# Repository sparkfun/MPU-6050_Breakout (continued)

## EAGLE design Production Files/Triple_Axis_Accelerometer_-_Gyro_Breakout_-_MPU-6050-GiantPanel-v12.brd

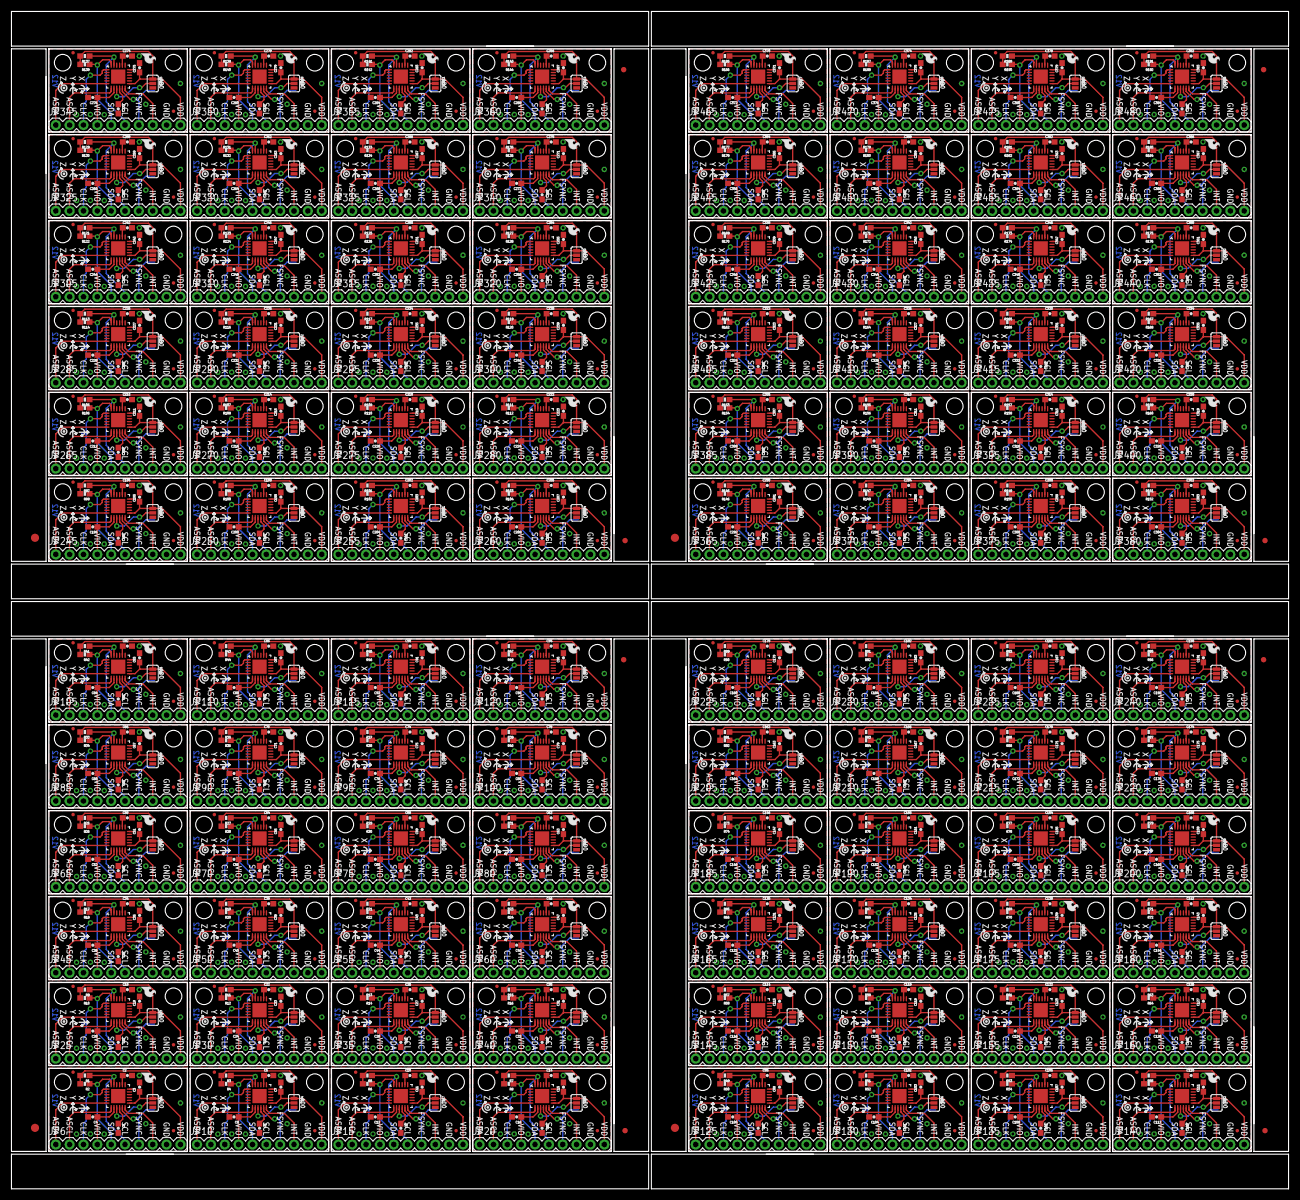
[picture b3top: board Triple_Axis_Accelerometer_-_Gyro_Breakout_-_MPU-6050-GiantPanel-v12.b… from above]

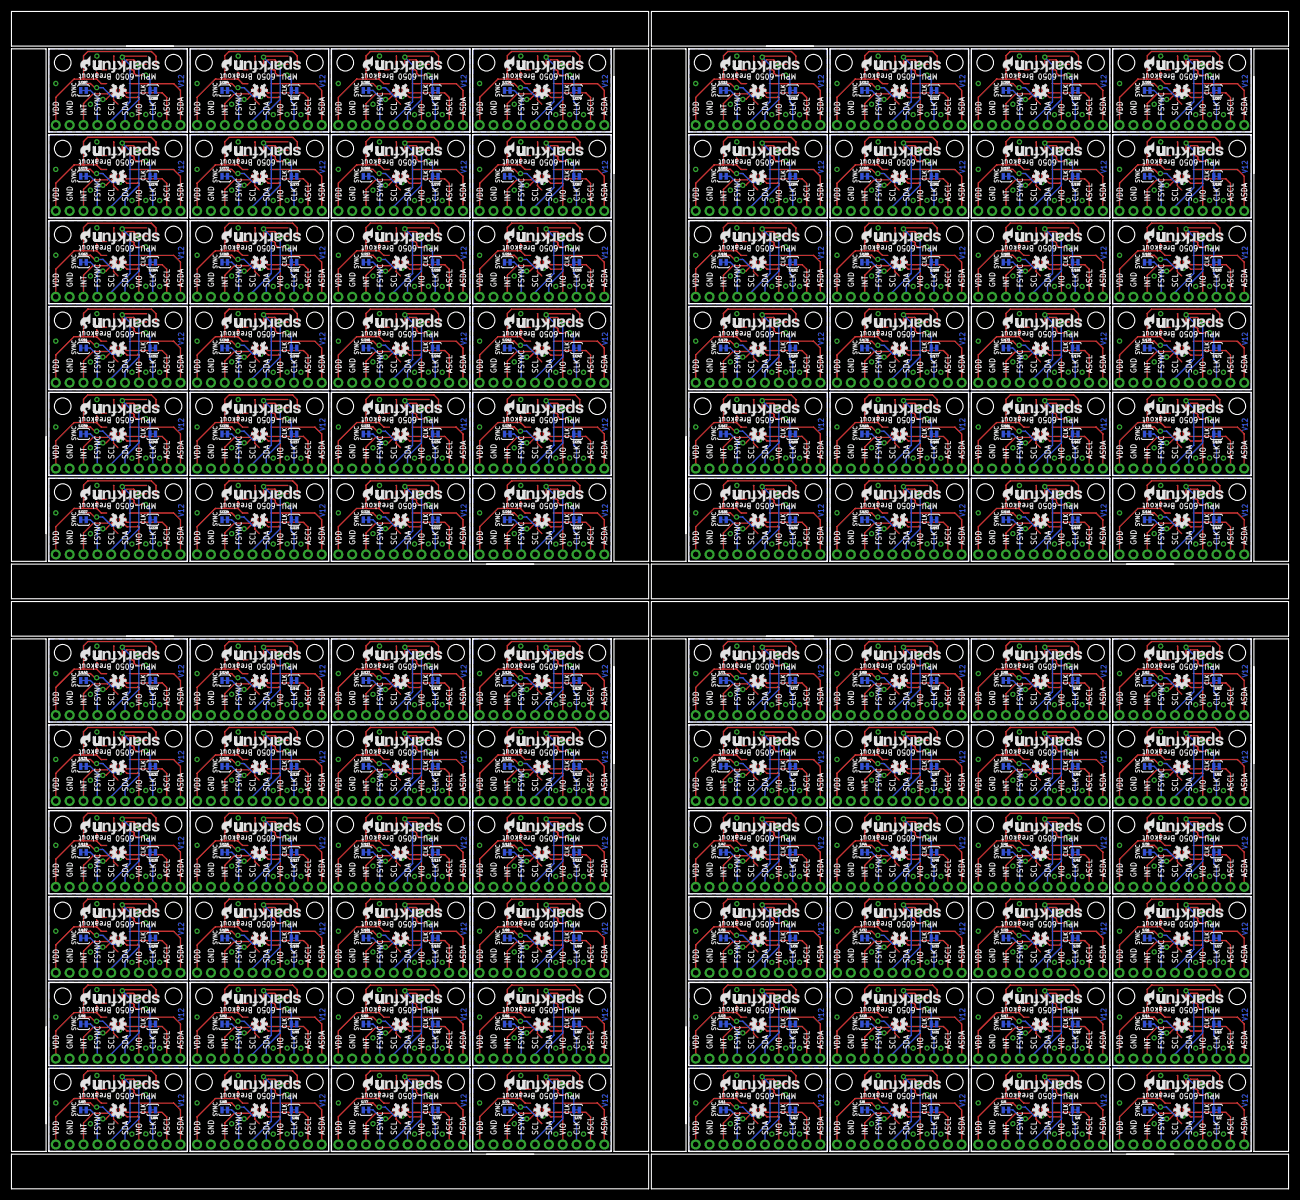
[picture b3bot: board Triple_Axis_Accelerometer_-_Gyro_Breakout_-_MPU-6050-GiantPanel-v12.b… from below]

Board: 2 copper layers, 234.2 x 215.9 mm, 1836 parts (480 on the bottom side), 1248 nets.

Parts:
C1, C3, C5, C7, C9, C11, C13, C15, C17, C19, C21, C23, C25, C27, C29, C31, C33, C35, C37, C39, C41, C43, C45, C47, C49, C51, C53, C55, C57, C59, C61, C63, C65, C67, C69, C71, C73, C75, C77, C79, C81, C83, C85, C87, C89, C91, C93, C95, C97, C99, C101, C103, C105, C107, C109, C111, C113, C115, C117, C119, C121, C123, C125, C127, C129, C131, C133, C135, C137, C139, C141, C143, C145, C147, C149, C151, C153, C155, C157, C159, C161, C163, C165, C167, C169, C171, C173, C175, C177, C179, C181, C183, C185, C187, C189, C191, C193, C195, C197, C199, C201, C203, C205, C207, C209, C211, C213, C215, C217, C219, C221, C223, C225, C227, C229, C231, C233, C235, C237, C239, C241, C243, C245, C247, C249, C251, C253, C255, C257, C259, C261, C263, C265, C267, C269, C271, C273, C275, C277, C279, C281, C283, C285, C287, C289, C291, C293, C295, C297, C299, C301, C303, C305, C307, C309, C311, C313, C315, C317, C319, C321, C323, C325, C327, C329, C331, C333, C335, C337, C339, C341, C343, C345, C347, C349, C351, C353, C355, C357, C359, C361, C363, C365, C367, C369, C371, C373, C375, C377, C379, C381, C383: 0.1uF; 0603-CAP
C2, C6, C10, C14, C18, C22, C26, C30, C34, C38, C42, C46, C50, C54, C58, C62, C66, C70, C74, C78, C82, C86, C90, C94, C98, C102, C106, C110, C114, C118, C122, C126, C130, C134, C138, C142, C146, C150, C154, C158, C162, C166, C170, C174, C178, C182, C186, C190, C194, C198, C202, C206, C210, C214, C218, C222, C226, C230, C234, C238, C242, C246, C250, C254, C258, C262, C266, C270, C274, C278, C282, C286, C290, C294, C298, C302, C306, C310, C314, C318, C322, C326, C330, C334, C338, C342, C346, C350, C354, C358, C362, C366, C370, C374, C378, C382: 2.2nF; 0603-CAP
C4, C8, C12, C16, C20, C24, C28, C32, C36, C40, C44, C48, C52, C56, C60, C64, C68, C72, C76, C80, C84, C88, C92, C96, C100, C104, C108, C112, C116, C120, C124, C128, C132, C136, C140, C144, C148, C152, C156, C160, C164, C168, C172, C176, C180, C184, C188, C192, C196, C200, C204, C208, C212, C216, C220, C224, C228, C232, C236, C240, C244, C248, C252, C256, C260, C264, C268, C272, C276, C280, C284, C288, C292, C296, C300, C304, C308, C312, C316, C320, C324, C328, C332, C336, C340, C344, C348, C352, C356, C360, C364, C368, C372, C376, C380, C384: 10nF; 0603-CAP
E$1, E$6, E$9, E$12: FIDUCIAL-1.5X3
E$2, E$3, E$4, E$5, E$7, E$8, E$10, E$11: FIDUCIAL-1X2
JP1, JP3, JP4, JP7, JP11, JP12, JP16, JP17, JP21, JP22, JP26, JP27, JP31, JP32, JP36, JP37, JP41, JP42, JP46, JP47, JP51, JP52, JP56, JP57, JP61, JP62, JP66, JP67, JP71, JP72, JP76, JP77, JP81, JP82, JP86, JP87, JP91, JP92, JP96, JP97, JP101, JP102, JP106, JP107, JP111, JP112, JP116, JP117, JP121, JP122, JP126, JP127, JP131, JP132, JP136, JP137, JP141, JP142, JP146, JP147, JP151, JP152, JP156, JP157, JP161, JP162, JP166, JP167, JP171, JP172, JP176, JP177, JP181, JP182, JP186, JP187, JP191, JP192, JP196, JP197, JP201, JP202, JP206, JP207, JP211, JP212, JP216, JP217, JP221, JP222, JP226, JP227, JP231, JP232, JP236, JP237, JP241, JP242, JP246, JP247, JP251, JP252, JP256, JP257, JP261, JP262, JP266, JP267, JP271, JP272, JP276, JP277, JP281, JP282, JP286, JP287, JP291, JP292, JP296, JP297, JP301, JP302, JP306, JP307, JP311, JP312, JP316, JP317, JP321, JP322, JP326, JP327, JP331, JP332, JP336, JP337, JP341, JP342, JP346, JP347, JP351, JP352, JP356, JP357, JP361, JP362, JP366, JP367, JP371, JP372, JP376, JP377, JP381, JP382, JP386, JP387, JP391, JP392, JP396, JP397, JP401, JP402, JP406, JP407, JP411, JP412, JP416, JP417, JP421, JP422, JP426, JP427, JP431, JP432, JP436, JP437, JP441, JP442, JP446, JP447, JP451, JP452, JP456, JP457, JP461, JP462, JP466, JP467, JP471, JP472, JP476, JP477: STAND-OFFTIGHT; STAND-OFF-TIGHT
JP2, JP5, JP8, JP9, JP13, JP14, JP18, JP19, JP23, JP24, JP28, JP29, JP33, JP34, JP38, JP39, JP43, JP44, JP48, JP49, JP53, JP54, JP58, JP59, JP63, JP64, JP68, JP69, JP73, JP74, JP78, JP79, JP83, JP84, JP88, JP89, JP93, JP94, JP98, JP99, JP103, JP104, JP108, JP109, JP113, JP114, JP118, JP119, JP123, JP124, JP128, JP129, JP133, JP134, JP138, JP139, JP143, JP144, JP148, JP149, JP153, JP154, JP158, JP159, JP163, JP164, JP168, JP169, JP173, JP174, JP178, JP179, JP183, JP184, JP188, JP189, JP193, JP194, JP198, JP199, JP203, JP204, JP208, JP209, JP213, JP214, JP218, JP219, JP223, JP224, JP228, JP229, JP233, JP234, JP238, JP239, JP243, JP244, JP248, JP249, JP253, JP254, JP258, JP259, JP263, JP264, JP268, JP269, JP273, JP274, JP278, JP279, JP283, JP284, JP288, JP289, JP293, JP294, JP298, JP299, JP303, JP304, JP308, JP309, JP313, JP314, JP318, JP319, JP323, JP324, JP328, JP329, JP333, JP334, JP338, JP339, JP343, JP344, JP348, JP349, JP353, JP354, JP358, JP359, JP363, JP364, JP368, JP369, JP373, JP374, JP378, JP379, JP383, JP384, JP388, JP389, JP393, JP394, JP398, JP399, JP403, JP404, JP408, JP409, JP413, JP414, JP418, JP419, JP423, JP424, JP428, JP429, JP433, JP434, JP438, JP439, JP443, JP444, JP448, JP449, JP453, JP454, JP458, JP459, JP463, JP464, JP468, JP469, JP473, JP474, JP478, JP479: FIDUCIALUFIDUCIAL; MICRO-FIDUCIAL
JP6, JP10, JP15, JP20, JP25, JP30, JP35, JP40, JP45, JP50, JP55, JP60, JP65, JP70, JP75, JP80, JP85, JP90, JP95, JP100, JP105, JP110, JP115, JP120, JP125, JP130, JP135, JP140, JP145, JP150, JP155, JP160, JP165, JP170, JP175, JP180, JP185, JP190, JP195, JP200, JP205, JP210, JP215, JP220, JP225, JP230, JP235, JP240, JP245, JP250, JP255, JP260, JP265, JP270, JP275, JP280, JP285, JP290, JP295, JP300, JP305, JP310, JP315, JP320, JP325, JP330, JP335, JP340, JP345, JP350, JP355, JP360, JP365, JP370, JP375, JP380, JP385, JP390, JP395, JP400, JP405, JP410, JP415, JP420, JP425, JP430, JP435, JP440, JP445, JP450, JP455, JP460, JP465, JP470, JP475, JP480: M10"; 1X10
R1, R2, R3, R4, R5, R6, R7, R8, R9, R10, R11, R12, R13, R14, R15, R16, R17, R18, R19, R20, R21, R22, R23, R24, R25, R26, R27, R28, R29, R30, R31, R32, R33, R34, R35, R36, R37, R38, R39, R40, R41, R42, R43, R44, R45, R46, R47, R48, R49, R50, R51, R52, R53, R54, R55, R56, R57, R58, R59, R60, R61, R62, R63, R64, R65, R66, R67, R68, R69, R70, R71, R72, R73, R74, R75, R76, R77, R78, R79, R80, R81, R82, R83, R84, R85, R86, R87, R88, R89, R90, R91, R92, R93, R94, R95, R96, R97, R98, R99, R100, R101, R102, R103, R104, R105, R106, R107, R108, R109, R110, R111, R112, R113, R114, R115, R116, R117, R118, R119, R120, R121, R122, R123, R124, R125, R126, R127, R128, R129, R130, R131, R132, R133, R134, R135, R136, R137, R138, R139, R140, R141, R142, R143, R144, R145, R146, R147, R148, R149, R150, R151, R152, R153, R154, R155, R156, R157, R158, R159, R160, R161, R162, R163, R164, R165, R166, R167, R168, R169, R170, R171, R172, R173, R174, R175, R176, R177, R178, R179, R180, R181, R182, R183, R184, R185, R186, R187, R188, R189, R190, R191, R192: 10k; 0603-RES
SJ1, SJ4, SJ7, SJ10, SJ13, SJ16, SJ19, SJ22, SJ25, SJ28, SJ31, SJ34, SJ37, SJ40, SJ43, SJ46, SJ49, SJ52, SJ55, SJ58, SJ61, SJ64, SJ67, SJ70, SJ73, SJ76, SJ79, SJ82, SJ85, SJ88, SJ91, SJ94, SJ97, SJ100, SJ103, SJ106, SJ109, SJ112, SJ115, SJ118, SJ121, SJ124, SJ127, SJ130, SJ133, SJ136, SJ139, SJ142, SJ145, SJ148, SJ151, SJ154, SJ157, SJ160, SJ163, SJ166, SJ169, SJ172, SJ175, SJ178, SJ181, SJ184, SJ187, SJ190, SJ193, SJ196, SJ199, SJ202, SJ205, SJ208, SJ211, SJ214, SJ217, SJ220, SJ223, SJ226, SJ229, SJ232, SJ235, SJ238, SJ241, SJ244, SJ247, SJ250, SJ253, SJ256, SJ259, SJ262, SJ265, SJ268, SJ271, SJ274, SJ277, SJ280, SJ283, SJ286: SJ_3_PASTE2&3
SJ2, SJ3, SJ5, SJ6, SJ8, SJ9, SJ11, SJ12, SJ14, SJ15, SJ17, SJ18, SJ20, SJ21, SJ23, SJ24, SJ26, SJ27, SJ29, SJ30, SJ32, SJ33, SJ35, SJ36, SJ38, SJ39, SJ41, SJ42, SJ44, SJ45, SJ47, SJ48, SJ50, SJ51, SJ53, SJ54, SJ56, SJ57, SJ59, SJ60, SJ62, SJ63, SJ65, SJ66, SJ68, SJ69, SJ71, SJ72, SJ74, SJ75, SJ77, SJ78, SJ80, SJ81, SJ83, SJ84, SJ86, SJ87, SJ89, SJ90, SJ92, SJ93, SJ95, SJ96, SJ98, SJ99, SJ101, SJ102, SJ104, SJ105, SJ107, SJ108, SJ110, SJ111, SJ113, SJ114, SJ116, SJ117, SJ119, SJ120, SJ122, SJ123, SJ125, SJ126, SJ128, SJ129, SJ131, SJ132, SJ134, SJ135, SJ137, SJ138, SJ140, SJ141, SJ143, SJ144, SJ146, SJ147, SJ149, SJ150, SJ152, SJ153, SJ155, SJ156, SJ158, SJ159, SJ161, SJ162, SJ164, SJ165, SJ167, SJ168, SJ170, SJ171, SJ173, SJ174, SJ176, SJ177, SJ179, SJ180, SJ182, SJ183, SJ185, SJ186, SJ188, SJ189, SJ191, SJ192, SJ194, SJ195, SJ197, SJ198, SJ200, SJ201, SJ203, SJ204, SJ206, SJ207, SJ209, SJ210, SJ212, SJ213, SJ215, SJ216, SJ218, SJ219, SJ221, SJ222, SJ224, SJ225, SJ227, SJ228, SJ230, SJ231, SJ233, SJ234, SJ236, SJ237, SJ239, SJ240, SJ242, SJ243, SJ245, SJ246, SJ248, SJ249, SJ251, SJ252, SJ254, SJ255, SJ257, SJ258, SJ260, SJ261, SJ263, SJ264, SJ266, SJ267, SJ269, SJ270, SJ272, SJ273, SJ275, SJ276, SJ278, SJ279, SJ281, SJ282, SJ284, SJ285, SJ287, SJ288: SJ_2S-TRACE
U1, U2, U3, U4, U5, U6, U7, U8, U9, U10, U11, U12, U13, U14, U15, U16, U17, U18, U19, U20, U21, U22, U23, U24, U25, U26, U27, U28, U29, U30, U31, U32, U33, U34, U35, U36, U37, U38, U39, U40, U41, U42, U43, U44, U45, U46, U47, U48, U49, U50, U51, U52, U53, U54, U55, U56, U57, U58, U59, U60, U61, U62, U63, U64, U65, U66, U67, U68, U69, U70, U71, U72, U73, U74, U75, U76, U77, U78, U79, U80, U81, U82, U83, U84, U85, U86, U87, U88, U89, U90, U91, U92, U93, U94, U95, U96: MPU-6050-1; QFN-24-4MM2
U$1, U$6, U$10, U$14, U$18, U$22, U$26, U$30, U$34, U$38, U$42, U$46, U$50, U$54, U$58, U$62, U$66, U$70, U$74, U$78, U$82, U$86, U$90, U$94, U$98, U$102, U$106, U$110, U$114, U$118, U$122, U$126, U$130, U$134, U$138, U$142, U$146, U$150, U$154, U$158, U$162, U$166, U$170, U$174, U$178, U$182, U$186, U$190, U$194, U$198, U$202, U$206, U$210, U$214, U$218, U$222, U$226, U$230, U$234, U$238, U$242, U$246, U$250, U$254, U$258, U$262, U$266, U$270, U$274, U$278, U$282, U$286, U$290, U$294, U$298, U$302, U$306, U$310, U$314, U$318, U$322, U$326, U$330, U$334, U$338, U$342, U$346, U$350, U$354, U$358, U$362, U$366, U$370, U$374, U$378, U$382: OSHW-LOGOS; OSHW-LOGO-S
U$2, U$3, U$5, U$7, U$9, U$11, U$13, U$15, U$17, U$19, U$21, U$23, U$25, U$27, U$29, U$31, U$33, U$35, U$37, U$39, U$41, U$43, U$45, U$47, U$49, U$51, U$53, U$55, U$57, U$59, U$61, U$63, U$65, U$67, U$69, U$71, U$73, U$75, U$77, U$79, U$81, U$83, U$85, U$87, U$89, U$91, U$93, U$95, U$97, U$99, U$101, U$103, U$105, U$107, U$109, U$111, U$113, U$115, U$117, U$119, U$121, U$123, U$125, U$127, U$129, U$131, U$133, U$135, U$137, U$139, U$141, U$143, U$145, U$147, U$149, U$151, U$153, U$155, U$157, U$159, U$161, U$163, U$165, U$167, U$169, U$171, U$173, U$175, U$177, U$179, U$181, U$183, U$185, U$187, U$189, U$191, U$193, U$195, U$197, U$199, U$201, U$203, U$205, U$207, U$209, U$211, U$213, U$215, U$217, U$219, U$221, U$223, U$225, U$227, U$229, U$231, U$233, U$235, U$237, U$239, U$241, U$243, U$245, U$247, U$249, U$251, U$253, U$255, U$257, U$259, U$261, U$263, U$265, U$267, U$269, U$271, U$273, U$275, U$277, U$279, U$281, U$283, U$285, U$287, U$289, U$291, U$293, U$295, U$297, U$299, U$301, U$303, U$305, U$307, U$309, U$311, U$313, U$315, U$317, U$319, U$321, U$323, U$325, U$327, U$329, U$331, U$333, U$335, U$337, U$339, U$341, U$343, U$345, U$347, U$349, U$351, U$353, U$355, U$357, U$359, U$361, U$363, U$365, U$367, U$369, U$371, U$373, U$375, U$377, U$379, U$381, U$383: SFE-LOGO-FLAME
U$4, U$8, U$12, U$16, U$20, U$24, U$28, U$32, U$36, U$40, U$44, U$48, U$52, U$56, U$60, U$64, U$68, U$72, U$76, U$80, U$84, U$88, U$92, U$96, U$100, U$104, U$108, U$112, U$116, U$120, U$124, U$128, U$132, U$136, U$140, U$144, U$148, U$152, U$156, U$160, U$164, U$168, U$172, U$176, U$180, U$184, U$188, U$192, U$196, U$200, U$204, U$208, U$212, U$216, U$220, U$224, U$228, U$232, U$236, U$240, U$244, U$248, U$252, U$256, U$260, U$264, U$268, U$272, U$276, U$280, U$284, U$288, U$292, U$296, U$300, U$304, U$308, U$312, U$316, U$320, U$324, U$328, U$332, U$336, U$340, U$344, U$348, U$352, U$356, U$360, U$364, U$368, U$372, U$376, U$380, U$384: SFE-NEW-WEB

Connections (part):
ADO: SJ1.2, U1.9
ADO1: SJ4.2, U2.9
ADO2: SJ7.2, U3.9
ADO3: SJ10.2, U4.9
ADO4: SJ13.2, U5.9
ADO5: SJ16.2, U6.9
ADO6: SJ19.2, U7.9
ADO7: SJ22.2, U8.9
ADO8: SJ25.2, U9.9
ADO9: SJ28.2, U10.9
ADO10: SJ31.2, U11.9
ADO11: SJ34.2, U12.9
ADO12: SJ37.2, U13.9
ADO13: SJ40.2, U14.9
ADO14: SJ43.2, U15.9
ADO15: SJ46.2, U16.9
ADO16: SJ49.2, U17.9
ADO17: SJ52.2, U18.9
ADO18: SJ55.2, U19.9
ADO19: SJ58.2, U20.9
ADO20: SJ61.2, U21.9
ADO21: SJ64.2, U22.9
ADO22: SJ67.2, U23.9
ADO23: SJ70.2, U24.9
ADO24: SJ73.2, U25.9
ADO25: SJ76.2, U26.9
ADO26: SJ79.2, U27.9
ADO27: SJ82.2, U28.9
ADO28: SJ85.2, U29.9
ADO29: SJ88.2, U30.9
ADO30: SJ91.2, U31.9
ADO31: SJ94.2, U32.9
ADO32: SJ97.2, U33.9
ADO33: SJ100.2, U34.9
ADO34: SJ103.2, U35.9
ADO35: SJ106.2, U36.9
ADO36: SJ109.2, U37.9
ADO37: SJ112.2, U38.9
ADO38: SJ115.2, U39.9
ADO39: SJ118.2, U40.9
ADO40: SJ121.2, U41.9
ADO41: SJ124.2, U42.9
ADO42: SJ127.2, U43.9
ADO43: SJ130.2, U44.9
ADO44: SJ133.2, U45.9
ADO45: SJ136.2, U46.9
ADO46: SJ139.2, U47.9
ADO47: SJ142.2, U48.9
ADO48: SJ145.2, U49.9
ADO49: SJ148.2, U50.9
ADO50: SJ151.2, U51.9
ADO51: SJ154.2, U52.9
ADO52: SJ157.2, U53.9
ADO53: SJ160.2, U54.9
ADO54: SJ163.2, U55.9
ADO55: SJ166.2, U56.9
ADO56: SJ169.2, U57.9
ADO57: SJ172.2, U58.9
ADO58: SJ175.2, U59.9
ADO59: SJ178.2, U60.9
ADO60: SJ181.2, U61.9
ADO61: SJ184.2, U62.9
ADO62: SJ187.2, U63.9
ADO63: SJ190.2, U64.9
ADO64: SJ193.2, U65.9
ADO65: SJ196.2, U66.9
ADO66: SJ199.2, U67.9
ADO67: SJ202.2, U68.9
ADO68: SJ205.2, U69.9
ADO69: SJ208.2, U70.9
ADO70: SJ211.2, U71.9
ADO71: SJ214.2, U72.9
ADO72: SJ217.2, U73.9
ADO73: SJ220.2, U74.9
ADO74: SJ223.2, U75.9
ADO75: SJ226.2, U76.9
ADO76: SJ229.2, U77.9
ADO77: SJ232.2, U78.9
ADO78: SJ235.2, U79.9
ADO79: SJ238.2, U80.9
ADO80: SJ241.2, U81.9
ADO81: SJ244.2, U82.9
ADO82: SJ247.2, U83.9
ADO83: SJ250.2, U84.9
ADO84: SJ253.2, U85.9
ADO85: SJ256.2, U86.9
ADO86: SJ259.2, U87.9
ADO87: SJ262.2, U88.9
ADO88: SJ265.2, U89.9
ADO89: SJ268.2, U90.9
ADO90: SJ271.2, U91.9
ADO91: SJ274.2, U92.9
ADO92: SJ277.2, U93.9
ADO93: SJ280.2, U94.9
ADO94: SJ283.2, U95.9
ADO95: SJ286.2, U96.9
AUX_SCL: JP6.2, U1.7
AUX_SCL1: JP10.2, U2.7
AUX_SCL2: JP15.2, U3.7
AUX_SCL3: JP20.2, U4.7
AUX_SCL4: JP25.2, U5.7
AUX_SCL5: JP30.2, U6.7
AUX_SCL6: JP35.2, U7.7
AUX_SCL7: JP40.2, U8.7
AUX_SCL8: JP45.2, U9.7
AUX_SCL9: JP50.2, U10.7
AUX_SCL10: JP55.2, U11.7
AUX_SCL11: JP60.2, U12.7
AUX_SCL12: JP65.2, U13.7
AUX_SCL13: JP70.2, U14.7
AUX_SCL14: JP75.2, U15.7
AUX_SCL15: JP80.2, U16.7
AUX_SCL16: JP85.2, U17.7
AUX_SCL17: JP90.2, U18.7
AUX_SCL18: JP95.2, U19.7
AUX_SCL19: JP100.2, U20.7
AUX_SCL20: JP105.2, U21.7
AUX_SCL21: JP110.2, U22.7
AUX_SCL22: JP115.2, U23.7
AUX_SCL23: JP120.2, U24.7
AUX_SCL24: JP125.2, U25.7
AUX_SCL25: JP130.2, U26.7
AUX_SCL26: JP135.2, U27.7
AUX_SCL27: JP140.2, U28.7
AUX_SCL28: JP145.2, U29.7
AUX_SCL29: JP150.2, U30.7
AUX_SCL30: JP155.2, U31.7
AUX_SCL31: JP160.2, U32.7
AUX_SCL32: JP165.2, U33.7
AUX_SCL33: JP170.2, U34.7
AUX_SCL34: JP175.2, U35.7
AUX_SCL35: JP180.2, U36.7
AUX_SCL36: JP185.2, U37.7
AUX_SCL37: JP190.2, U38.7
AUX_SCL38: JP195.2, U39.7
AUX_SCL39: JP200.2, U40.7
AUX_SCL40: JP205.2, U41.7
AUX_SCL41: JP210.2, U42.7
AUX_SCL42: JP215.2, U43.7
AUX_SCL43: JP220.2, U44.7
AUX_SCL44: JP225.2, U45.7
AUX_SCL45: JP230.2, U46.7
AUX_SCL46: JP235.2, U47.7
AUX_SCL47: JP240.2, U48.7
AUX_SCL48: JP245.2, U49.7
AUX_SCL49: JP250.2, U50.7
AUX_SCL50: JP255.2, U51.7
AUX_SCL51: JP260.2, U52.7
AUX_SCL52: JP265.2, U53.7
AUX_SCL53: JP270.2, U54.7
AUX_SCL54: JP275.2, U55.7
AUX_SCL55: JP280.2, U56.7
AUX_SCL56: JP285.2, U57.7
AUX_SCL57: JP290.2, U58.7
AUX_SCL58: JP295.2, U59.7
AUX_SCL59: JP300.2, U60.7
AUX_SCL60: JP305.2, U61.7
AUX_SCL61: JP310.2, U62.7
AUX_SCL62: JP315.2, U63.7
AUX_SCL63: JP320.2, U64.7
AUX_SCL64: JP325.2, U65.7
AUX_SCL65: JP330.2, U66.7
AUX_SCL66: JP335.2, U67.7
AUX_SCL67: JP340.2, U68.7
AUX_SCL68: JP345.2, U69.7
AUX_SCL69: JP350.2, U70.7
AUX_SCL70: JP355.2, U71.7
AUX_SCL71: JP360.2, U72.7
AUX_SCL72: JP365.2, U73.7
AUX_SCL73: JP370.2, U74.7
AUX_SCL74: JP375.2, U75.7
AUX_SCL75: JP380.2, U76.7
AUX_SCL76: JP385.2, U77.7
AUX_SCL77: JP390.2, U78.7
AUX_SCL78: JP395.2, U79.7
AUX_SCL79: JP400.2, U80.7
AUX_SCL80: JP405.2, U81.7
AUX_SCL81: JP410.2, U82.7
AUX_SCL82: JP415.2, U83.7
AUX_SCL83: JP420.2, U84.7
AUX_SCL84: JP425.2, U85.7
AUX_SCL85: JP430.2, U86.7
AUX_SCL86: JP435.2, U87.7
AUX_SCL87: JP440.2, U88.7
AUX_SCL88: JP445.2, U89.7
AUX_SCL89: JP450.2, U90.7
AUX_SCL90: JP455.2, U91.7
AUX_SCL91: JP460.2, U92.7
AUX_SCL92: JP465.2, U93.7
AUX_SCL93: JP470.2, U94.7
AUX_SCL94: JP475.2, U95.7
AUX_SCL95: JP480.2, U96.7
AUX_SDA: JP6.1, U1.6
AUX_SDA1: JP10.1, U2.6
AUX_SDA2: JP15.1, U3.6
AUX_SDA3: JP20.1, U4.6
AUX_SDA4: JP25.1, U5.6
AUX_SDA5: JP30.1, U6.6
AUX_SDA6: JP35.1, U7.6
AUX_SDA7: JP40.1, U8.6
AUX_SDA8: JP45.1, U9.6
AUX_SDA9: JP50.1, U10.6
AUX_SDA10: JP55.1, U11.6
AUX_SDA11: JP60.1, U12.6
AUX_SDA12: JP65.1, U13.6
AUX_SDA13: JP70.1, U14.6
AUX_SDA14: JP75.1, U15.6
AUX_SDA15: JP80.1, U16.6
AUX_SDA16: JP85.1, U17.6
AUX_SDA17: JP90.1, U18.6
AUX_SDA18: JP95.1, U19.6
AUX_SDA19: JP100.1, U20.6
AUX_SDA20: JP105.1, U21.6
AUX_SDA21: JP110.1, U22.6
AUX_SDA22: JP115.1, U23.6
AUX_SDA23: JP120.1, U24.6
AUX_SDA24: JP125.1, U25.6
AUX_SDA25: JP130.1, U26.6
AUX_SDA26: JP135.1, U27.6
AUX_SDA27: JP140.1, U28.6
AUX_SDA28: JP145.1, U29.6
AUX_SDA29: JP150.1, U30.6
AUX_SDA30: JP155.1, U31.6
AUX_SDA31: JP160.1, U32.6
AUX_SDA32: JP165.1, U33.6
AUX_SDA33: JP170.1, U34.6
AUX_SDA34: JP175.1, U35.6
AUX_SDA35: JP180.1, U36.6
AUX_SDA36: JP185.1, U37.6
AUX_SDA37: JP190.1, U38.6
AUX_SDA38: JP195.1, U39.6
AUX_SDA39: JP200.1, U40.6
AUX_SDA40: JP205.1, U41.6
AUX_SDA41: JP210.1, U42.6
AUX_SDA42: JP215.1, U43.6
AUX_SDA43: JP220.1, U44.6
AUX_SDA44: JP225.1, U45.6
AUX_SDA45: JP230.1, U46.6
AUX_SDA46: JP235.1, U47.6
AUX_SDA47: JP240.1, U48.6
AUX_SDA48: JP245.1, U49.6
AUX_SDA49: JP250.1, U50.6
AUX_SDA50: JP255.1, U51.6
AUX_SDA51: JP260.1, U52.6
AUX_SDA52: JP265.1, U53.6
AUX_SDA53: JP270.1, U54.6
AUX_SDA54: JP275.1, U55.6
AUX_SDA55: JP280.1, U56.6
AUX_SDA56: JP285.1, U57.6
AUX_SDA57: JP290.1, U58.6
AUX_SDA58: JP295.1, U59.6
AUX_SDA59: JP300.1, U60.6
AUX_SDA60: JP305.1, U61.6
AUX_SDA61: JP310.1, U62.6
AUX_SDA62: JP315.1, U63.6
AUX_SDA63: JP320.1, U64.6
AUX_SDA64: JP325.1, U65.6
AUX_SDA65: JP330.1, U66.6
AUX_SDA66: JP335.1, U67.6
AUX_SDA67: JP340.1, U68.6
AUX_SDA68: JP345.1, U69.6
AUX_SDA69: JP350.1, U70.6
AUX_SDA70: JP355.1, U71.6
AUX_SDA71: JP360.1, U72.6
AUX_SDA72: JP365.1, U73.6
AUX_SDA73: JP370.1, U74.6
AUX_SDA74: JP375.1, U75.6
AUX_SDA75: JP380.1, U76.6
AUX_SDA76: JP385.1, U77.6
AUX_SDA77: JP390.1, U78.6
AUX_SDA78: JP395.1, U79.6
AUX_SDA79: JP400.1, U80.6
AUX_SDA80: JP405.1, U81.6
AUX_SDA81: JP410.1, U82.6
AUX_SDA82: JP415.1, U83.6
AUX_SDA83: JP420.1, U84.6
AUX_SDA84: JP425.1, U85.6
AUX_SDA85: JP430.1, U86.6
AUX_SDA86: JP435.1, U87.6
AUX_SDA87: JP440.1, U88.6
AUX_SDA88: JP445.1, U89.6
AUX_SDA89: JP450.1, U90.6
AUX_SDA90: JP455.1, U91.6
AUX_SDA91: JP460.1, U92.6
AUX_SDA92: JP465.1, U93.6
AUX_SDA93: JP470.1, U94.6
AUX_SDA94: JP475.1, U95.6
AUX_SDA95: JP480.1, U96.6
CLKIN: JP6.3, SJ2.2, U1.1
CLKIN1: JP10.3, SJ6.2, U2.1
CLKIN2: JP15.3, SJ9.2, U3.1
CLKIN3: JP20.3, SJ12.2, U4.1
CLKIN4: JP25.3, SJ15.2, U5.1
CLKIN5: JP30.3, SJ18.2, U6.1
CLKIN6: JP35.3, SJ21.2, U7.1
CLKIN7: JP40.3, SJ24.2, U8.1
CLKIN8: JP45.3, SJ27.2, U9.1
CLKIN9: JP50.3, SJ30.2, U10.1
CLKIN10: JP55.3, SJ33.2, U11.1
CLKIN11: JP60.3, SJ36.2, U12.1
CLKIN12: JP65.3, SJ39.2, U13.1
CLKIN13: JP70.3, SJ42.2, U14.1
CLKIN14: JP75.3, SJ45.2, U15.1
CLKIN15: JP80.3, SJ48.2, U16.1
CLKIN16: JP85.3, SJ51.2, U17.1
CLKIN17: JP90.3, SJ54.2, U18.1
CLKIN18: JP95.3, SJ57.2, U19.1
CLKIN19: JP100.3, SJ60.2, U20.1
CLKIN20: JP105.3, SJ63.2, U21.1
CLKIN21: JP110.3, SJ66.2, U22.1
CLKIN22: JP115.3, SJ69.2, U23.1
CLKIN23: JP120.3, SJ72.2, U24.1
CLKIN24: JP125.3, SJ75.2, U25.1
CLKIN25: JP130.3, SJ78.2, U26.1
CLKIN26: JP135.3, SJ81.2, U27.1
CLKIN27: JP140.3, SJ84.2, U28.1
CLKIN28: JP145.3, SJ87.2, U29.1
CLKIN29: JP150.3, SJ90.2, U30.1
CLKIN30: JP155.3, SJ93.2, U31.1
CLKIN31: JP160.3, SJ96.2, U32.1
CLKIN32: JP165.3, SJ99.2, U33.1
CLKIN33: JP170.3, SJ102.2, U34.1
CLKIN34: JP175.3, SJ105.2, U35.1
CLKIN35: JP180.3, SJ108.2, U36.1
CLKIN36: JP185.3, SJ111.2, U37.1
CLKIN37: JP190.3, SJ114.2, U38.1
CLKIN38: JP195.3, SJ117.2, U39.1
CLKIN39: JP200.3, SJ120.2, U40.1
CLKIN40: JP205.3, SJ123.2, U41.1
CLKIN41: JP210.3, SJ126.2, U42.1
CLKIN42: JP215.3, SJ129.2, U43.1
CLKIN43: JP220.3, SJ132.2, U44.1
CLKIN44: JP225.3, SJ135.2, U45.1
CLKIN45: JP230.3, SJ138.2, U46.1
CLKIN46: JP235.3, SJ141.2, U47.1
CLKIN47: JP240.3, SJ144.2, U48.1
CLKIN48: JP245.3, SJ147.2, U49.1
CLKIN49: JP250.3, SJ150.2, U50.1
CLKIN50: JP255.3, SJ153.2, U51.1
CLKIN51: JP260.3, SJ156.2, U52.1
CLKIN52: JP265.3, SJ159.2, U53.1
CLKIN53: JP270.3, SJ162.2, U54.1
CLKIN54: JP275.3, SJ165.2, U55.1
CLKIN55: JP280.3, SJ168.2, U56.1
CLKIN56: JP285.3, SJ171.2, U57.1
CLKIN57: JP290.3, SJ174.2, U58.1
CLKIN58: JP295.3, SJ177.2, U59.1
CLKIN59: JP300.3, SJ180.2, U60.1
CLKIN60: JP305.3, SJ183.2, U61.1
CLKIN61: JP310.3, SJ186.2, U62.1
CLKIN62: JP315.3, SJ189.2, U63.1
CLKIN63: JP320.3, SJ192.2, U64.1
CLKIN64: JP325.3, SJ195.2, U65.1
CLKIN65: JP330.3, SJ198.2, U66.1
CLKIN66: JP335.3, SJ201.2, U67.1
CLKIN67: JP340.3, SJ204.2, U68.1
CLKIN68: JP345.3, SJ207.2, U69.1
CLKIN69: JP350.3, SJ210.2, U70.1
CLKIN70: JP355.3, SJ213.2, U71.1
CLKIN71: JP360.3, SJ216.2, U72.1
CLKIN72: JP365.3, SJ219.2, U73.1
CLKIN73: JP370.3, SJ222.2, U74.1
CLKIN74: JP375.3, SJ225.2, U75.1
CLKIN75: JP380.3, SJ228.2, U76.1
CLKIN76: JP385.3, SJ231.2, U77.1
CLKIN77: JP390.3, SJ234.2, U78.1
CLKIN78: JP395.3, SJ237.2, U79.1
CLKIN79: JP400.3, SJ240.2, U80.1
CLKIN80: JP405.3, SJ243.2, U81.1
CLKIN81: JP410.3, SJ246.2, U82.1
CLKIN82: JP415.3, SJ249.2, U83.1
CLKIN83: JP420.3, SJ252.2, U84.1
CLKIN84: JP425.3, SJ255.2, U85.1
CLKIN85: JP430.3, SJ258.2, U86.1
CLKIN86: JP435.3, SJ261.2, U87.1
CLKIN87: JP440.3, SJ264.2, U88.1
CLKIN88: JP445.3, SJ267.2, U89.1
CLKIN89: JP450.3, SJ270.2, U90.1
CLKIN90: JP455.3, SJ273.2, U91.1
CLKIN91: JP460.3, SJ276.2, U92.1
CLKIN92: JP465.3, SJ279.2, U93.1
CLKIN93: JP470.3, SJ282.2, U94.1
CLKIN94: JP475.3, SJ285.2, U95.1
CLKIN95: JP480.3, SJ288.2, U96.1
FSYNC: JP6.7, SJ3.2, U1.11
FSYNC1: JP10.7, SJ5.2, U2.11
FSYNC2: JP15.7, SJ8.2, U3.11
FSYNC3: JP20.7, SJ11.2, U4.11
FSYNC4: JP25.7, SJ14.2, U5.11
FSYNC5: JP30.7, SJ17.2, U6.11
FSYNC6: JP35.7, SJ20.2, U7.11
FSYNC7: JP40.7, SJ23.2, U8.11
FSYNC8: JP45.7, SJ26.2, U9.11
FSYNC9: JP50.7, SJ29.2, U10.11
FSYNC10: JP55.7, SJ32.2, U11.11
FSYNC11: JP60.7, SJ35.2, U12.11
FSYNC12: JP65.7, SJ38.2, U13.11
FSYNC13: JP70.7, SJ41.2, U14.11
FSYNC14: JP75.7, SJ44.2, U15.11
FSYNC15: JP80.7, SJ47.2, U16.11
FSYNC16: JP85.7, SJ50.2, U17.11
FSYNC17: JP90.7, SJ53.2, U18.11
FSYNC18: JP95.7, SJ56.2, U19.11
FSYNC19: JP100.7, SJ59.2, U20.11
FSYNC20: JP105.7, SJ62.2, U21.11
FSYNC21: JP110.7, SJ65.2, U22.11
FSYNC22: JP115.7, SJ68.2, U23.11
FSYNC23: JP120.7, SJ71.2, U24.11
FSYNC24: JP125.7, SJ74.2, U25.11
FSYNC25: JP130.7, SJ77.2, U26.11
FSYNC26: JP135.7, SJ80.2, U27.11
FSYNC27: JP140.7, SJ83.2, U28.11
FSYNC28: JP145.7, SJ86.2, U29.11
FSYNC29: JP150.7, SJ89.2, U30.11
FSYNC30: JP155.7, SJ92.2, U31.11
FSYNC31: JP160.7, SJ95.2, U32.11
FSYNC32: JP165.7, SJ98.2, U33.11
FSYNC33: JP170.7, SJ101.2, U34.11
FSYNC34: JP175.7, SJ104.2, U35.11
FSYNC35: JP180.7, SJ107.2, U36.11
FSYNC36: JP185.7, SJ110.2, U37.11
FSYNC37: JP190.7, SJ113.2, U38.11
FSYNC38: JP195.7, SJ116.2, U39.11
FSYNC39: JP200.7, SJ119.2, U40.11
FSYNC40: JP205.7, SJ122.2, U41.11
FSYNC41: JP210.7, SJ125.2, U42.11
FSYNC42: JP215.7, SJ128.2, U43.11
FSYNC43: JP220.7, SJ131.2, U44.11
FSYNC44: JP225.7, SJ134.2, U45.11
FSYNC45: JP230.7, SJ137.2, U46.11
FSYNC46: JP235.7, SJ140.2, U47.11
FSYNC47: JP240.7, SJ143.2, U48.11
FSYNC48: JP245.7, SJ146.2, U49.11
FSYNC49: JP250.7, SJ149.2, U50.11
FSYNC50: JP255.7, SJ152.2, U51.11
FSYNC51: JP260.7, SJ155.2, U52.11
FSYNC52: JP265.7, SJ158.2, U53.11
FSYNC53: JP270.7, SJ161.2, U54.11
FSYNC54: JP275.7, SJ164.2, U55.11
FSYNC55: JP280.7, SJ167.2, U56.11
FSYNC56: JP285.7, SJ170.2, U57.11
FSYNC57: JP290.7, SJ173.2, U58.11
FSYNC58: JP295.7, SJ176.2, U59.11
FSYNC59: JP300.7, SJ179.2, U60.11
FSYNC60: JP305.7, SJ182.2, U61.11
FSYNC61: JP310.7, SJ185.2, U62.11
FSYNC62: JP315.7, SJ188.2, U63.11
FSYNC63: JP320.7, SJ191.2, U64.11
FSYNC64: JP325.7, SJ194.2, U65.11
FSYNC65: JP330.7, SJ197.2, U66.11
FSYNC66: JP335.7, SJ200.2, U67.11
FSYNC67: JP340.7, SJ203.2, U68.11
FSYNC68: JP345.7, SJ206.2, U69.11
FSYNC69: JP350.7, SJ209.2, U70.11
FSYNC70: JP355.7, SJ212.2, U71.11
FSYNC71: JP360.7, SJ215.2, U72.11
FSYNC72: JP365.7, SJ218.2, U73.11
FSYNC73: JP370.7, SJ221.2, U74.11
FSYNC74: JP375.7, SJ224.2, U75.11
FSYNC75: JP380.7, SJ227.2, U76.11
FSYNC76: JP385.7, SJ230.2, U77.11
FSYNC77: JP390.7, SJ233.2, U78.11
FSYNC78: JP395.7, SJ236.2, U79.11
FSYNC79: JP400.7, SJ239.2, U80.11
FSYNC80: JP405.7, SJ242.2, U81.11
FSYNC81: JP410.7, SJ245.2, U82.11
FSYNC82: JP415.7, SJ248.2, U83.11
FSYNC83: JP420.7, SJ251.2, U84.11
FSYNC84: JP425.7, SJ254.2, U85.11
FSYNC85: JP430.7, SJ257.2, U86.11
FSYNC86: JP435.7, SJ260.2, U87.11
FSYNC87: JP440.7, SJ263.2, U88.11
FSYNC88: JP445.7, SJ266.2, U89.11
FSYNC89: JP450.7, SJ269.2, U90.11
FSYNC90: JP455.7, SJ272.2, U91.11
FSYNC91: JP460.7, SJ275.2, U92.11
FSYNC92: JP465.7, SJ278.2, U93.11
FSYNC93: JP470.7, SJ281.2, U94.11
FSYNC94: JP475.7, SJ284.2, U95.11
FSYNC95: JP480.7, SJ287.2, U96.11
GND: C1.2, C2.2, C3.2, C4.2, JP6.9, SJ1.3, SJ2.1, SJ3.1, U1.18
GND1: C5.2, C6.2, C7.2, C8.2, JP10.9, SJ4.3, SJ5.1, SJ6.1, U2.18
GND2: C9.2, C10.2, C11.2, C12.2, JP15.9, SJ7.3, SJ8.1, SJ9.1, U3.18
GND3: C13.2, C14.2, C15.2, C16.2, JP20.9, SJ10.3, SJ11.1, SJ12.1, U4.18
GND4: C17.2, C18.2, C19.2, C20.2, JP25.9, SJ13.3, SJ14.1, SJ15.1, U5.18
GND5: C21.2, C22.2, C23.2, C24.2, JP30.9, SJ16.3, SJ17.1, SJ18.1, U6.18
GND6: C25.2, C26.2, C27.2, C28.2, JP35.9, SJ19.3, SJ20.1, SJ21.1, U7.18
GND7: C29.2, C30.2, C31.2, C32.2, JP40.9, SJ22.3, SJ23.1, SJ24.1, U8.18
GND8: C33.2, C34.2, C35.2, C36.2, JP45.9, SJ25.3, SJ26.1, SJ27.1, U9.18
GND9: C37.2, C38.2, C39.2, C40.2, JP50.9, SJ28.3, SJ29.1, SJ30.1, U10.18
GND10: C41.2, C42.2, C43.2, C44.2, JP55.9, SJ31.3, SJ32.1, SJ33.1, U11.18
GND11: C45.2, C46.2, C47.2, C48.2, JP60.9, SJ34.3, SJ35.1, SJ36.1, U12.18
GND12: C49.2, C50.2, C51.2, C52.2, JP65.9, SJ37.3, SJ38.1, SJ39.1, U13.18
GND13: C53.2, C54.2, C55.2, C56.2, JP70.9, SJ40.3, SJ41.1, SJ42.1, U14.18
GND14: C57.2, C58.2, C59.2, C60.2, JP75.9, SJ43.3, SJ44.1, SJ45.1, U15.18
GND15: C61.2, C62.2, C63.2, C64.2, JP80.9, SJ46.3, SJ47.1, SJ48.1, U16.18
GND16: C65.2, C66.2, C67.2, C68.2, JP85.9, SJ49.3, SJ50.1, SJ51.1, U17.18
GND17: C69.2, C70.2, C71.2, C72.2, JP90.9, SJ52.3, SJ53.1, SJ54.1, U18.18
GND18: C73.2, C74.2, C75.2, C76.2, JP95.9, SJ55.3, SJ56.1, SJ57.1, U19.18
GND19: C77.2, C78.2, C79.2, C80.2, JP100.9, SJ58.3, SJ59.1, SJ60.1, U20.18
GND20: C81.2, C82.2, C83.2, C84.2, JP105.9, SJ61.3, SJ62.1, SJ63.1, U21.18
GND21: C85.2, C86.2, C87.2, C88.2, JP110.9, SJ64.3, SJ65.1, SJ66.1, U22.18
GND22: C89.2, C90.2, C91.2, C92.2, JP115.9, SJ67.3, SJ68.1, SJ69.1, U23.18
GND23: C93.2, C94.2, C95.2, C96.2, JP120.9, SJ70.3, SJ71.1, SJ72.1, U24.18
GND24: C97.2, C98.2, C99.2, C100.2, JP125.9, SJ73.3, SJ74.1, SJ75.1, U25.18
GND25: C101.2, C102.2, C103.2, C104.2, JP130.9, SJ76.3, SJ77.1, SJ78.1, U26.18
GND26: C105.2, C106.2, C107.2, C108.2, JP135.9, SJ79.3, SJ80.1, SJ81.1, U27.18
GND27: C109.2, C110.2, C111.2, C112.2, JP140.9, SJ82.3, SJ83.1, SJ84.1, U28.18
GND28: C113.2, C114.2, C115.2, C116.2, JP145.9, SJ85.3, SJ86.1, SJ87.1, U29.18
GND29: C117.2, C118.2, C119.2, C120.2, JP150.9, SJ88.3, SJ89.1, SJ90.1, U30.18
GND30: C121.2, C122.2, C123.2, C124.2, JP155.9, SJ91.3, SJ92.1, SJ93.1, U31.18
GND31: C125.2, C126.2, C127.2, C128.2, JP160.9, SJ94.3, SJ95.1, SJ96.1, U32.18
GND32: C129.2, C130.2, C131.2, C132.2, JP165.9, SJ97.3, SJ98.1, SJ99.1, U33.18
GND33: C133.2, C134.2, C135.2, C136.2, JP170.9, SJ100.3, SJ101.1, SJ102.1, U34.18
GND34: C137.2, C138.2, C139.2, C140.2, JP175.9, SJ103.3, SJ104.1, SJ105.1, U35.18
GND35: C141.2, C142.2, C143.2, C144.2, JP180.9, SJ106.3, SJ107.1, SJ108.1, U36.18
GND36: C145.2, C146.2, C147.2, C148.2, JP185.9, SJ109.3, SJ110.1, SJ111.1, U37.18
GND37: C149.2, C150.2, C151.2, C152.2, JP190.9, SJ112.3, SJ113.1, SJ114.1, U38.18
GND38: C153.2, C154.2, C155.2, C156.2, JP195.9, SJ115.3, SJ116.1, SJ117.1, U39.18
GND39: C157.2, C158.2, C159.2, C160.2, JP200.9, SJ118.3, SJ119.1, SJ120.1, U40.18
GND40: C161.2, C162.2, C163.2, C164.2, JP205.9, SJ121.3, SJ122.1, SJ123.1, U41.18
GND41: C165.2, C166.2, C167.2, C168.2, JP210.9, SJ124.3, SJ125.1, SJ126.1, U42.18
GND42: C169.2, C170.2, C171.2, C172.2, JP215.9, SJ127.3, SJ128.1, SJ129.1, U43.18
GND43: C173.2, C174.2, C175.2, C176.2, JP220.9, SJ130.3, SJ131.1, SJ132.1, U44.18
GND44: C177.2, C178.2, C179.2, C180.2, JP225.9, SJ133.3, SJ134.1, SJ135.1, U45.18
GND45: C181.2, C182.2, C183.2, C184.2, JP230.9, SJ136.3, SJ137.1, SJ138.1, U46.18
GND46: C185.2, C186.2, C187.2, C188.2, JP235.9, SJ139.3, SJ140.1, SJ141.1, U47.18
GND47: C189.2, C190.2, C191.2, C192.2, JP240.9, SJ142.3, SJ143.1, SJ144.1, U48.18
GND48: C193.2, C194.2, C195.2, C196.2, JP245.9, SJ145.3, SJ146.1, SJ147.1, U49.18
GND49: C197.2, C198.2, C199.2, C200.2, JP250.9, SJ148.3, SJ149.1, SJ150.1, U50.18
GND50: C201.2, C202.2, C203.2, C204.2, JP255.9, SJ151.3, SJ152.1, SJ153.1, U51.18
GND51: C205.2, C206.2, C207.2, C208.2, JP260.9, SJ154.3, SJ155.1, SJ156.1, U52.18
GND52: C209.2, C210.2, C211.2, C212.2, JP265.9, SJ157.3, SJ158.1, SJ159.1, U53.18
GND53: C213.2, C214.2, C215.2, C216.2, JP270.9, SJ160.3, SJ161.1, SJ162.1, U54.18
GND54: C217.2, C218.2, C219.2, C220.2, JP275.9, SJ163.3, SJ164.1, SJ165.1, U55.18
GND55: C221.2, C222.2, C223.2, C224.2, JP280.9, SJ166.3, SJ167.1, SJ168.1, U56.18
GND56: C225.2, C226.2, C227.2, C228.2, JP285.9, SJ169.3, SJ170.1, SJ171.1, U57.18
GND57: C229.2, C230.2, C231.2, C232.2, JP290.9, SJ172.3, SJ173.1, SJ174.1, U58.18
GND58: C233.2, C234.2, C235.2, C236.2, JP295.9, SJ175.3, SJ176.1, SJ177.1, U59.18
GND59: C237.2, C238.2, C239.2, C240.2, JP300.9, SJ178.3, SJ179.1, SJ180.1, U60.18
GND60: C241.2, C242.2, C243.2, C244.2, JP305.9, SJ181.3, SJ182.1, SJ183.1, U61.18
GND61: C245.2, C246.2, C247.2, C248.2, JP310.9, SJ184.3, SJ185.1, SJ186.1, U62.18
GND62: C249.2, C250.2, C251.2, C252.2, JP315.9, SJ187.3, SJ188.1, SJ189.1, U63.18
GND63: C253.2, C254.2, C255.2, C256.2, JP320.9, SJ190.3, SJ191.1, SJ192.1, U64.18
GND64: C257.2, C258.2, C259.2, C260.2, JP325.9, SJ193.3, SJ194.1, SJ195.1, U65.18
GND65: C261.2, C262.2, C263.2, C264.2, JP330.9, SJ196.3, SJ197.1, SJ198.1, U66.18
GND66: C265.2, C266.2, C267.2, C268.2, JP335.9, SJ199.3, SJ200.1, SJ201.1, U67.18
GND67: C269.2, C270.2, C271.2, C272.2, JP340.9, SJ202.3, SJ203.1, SJ204.1, U68.18
GND68: C273.2, C274.2, C275.2, C276.2, JP345.9, SJ205.3, SJ206.1, SJ207.1, U69.18
GND69: C277.2, C278.2, C279.2, C280.2, JP350.9, SJ208.3, SJ209.1, SJ210.1, U70.18
GND70: C281.2, C282.2, C283.2, C284.2, JP355.9, SJ211.3, SJ212.1, SJ213.1, U71.18
GND71: C285.2, C286.2, C287.2, C288.2, JP360.9, SJ214.3, SJ215.1, SJ216.1, U72.18
GND72: C289.2, C290.2, C291.2, C292.2, JP365.9, SJ217.3, SJ218.1, SJ219.1, U73.18
GND73: C293.2, C294.2, C295.2, C296.2, JP370.9, SJ220.3, SJ221.1, SJ222.1, U74.18
GND74: C297.2, C298.2, C299.2, C300.2, JP375.9, SJ223.3, SJ224.1, SJ225.1, U75.18
GND75: C301.2, C302.2, C303.2, C304.2, JP380.9, SJ226.3, SJ227.1, SJ228.1, U76.18
GND76: C305.2, C306.2, C307.2, C308.2, JP385.9, SJ229.3, SJ230.1, SJ231.1, U77.18
GND77: C309.2, C310.2, C311.2, C312.2, JP390.9, SJ232.3, SJ233.1, SJ234.1, U78.18
GND78: C313.2, C314.2, C315.2, C316.2, JP395.9, SJ235.3, SJ236.1, SJ237.1, U79.18
GND79: C317.2, C318.2, C319.2, C320.2, JP400.9, SJ238.3, SJ239.1, SJ240.1, U80.18
GND80: C321.2, C322.2, C323.2, C324.2, JP405.9, SJ241.3, SJ242.1, SJ243.1, U81.18
GND81: C325.2, C326.2, C327.2, C328.2, JP410.9, SJ244.3, SJ245.1, SJ246.1, U82.18
GND82: C329.2, C330.2, C331.2, C332.2, JP415.9, SJ247.3, SJ248.1, SJ249.1, U83.18
GND83: C333.2, C334.2, C335.2, C336.2, JP420.9, SJ250.3, SJ251.1, SJ252.1, U84.18
GND84: C337.2, C338.2, C339.2, C340.2, JP425.9, SJ253.3, SJ254.1, SJ255.1, U85.18
GND85: C341.2, C342.2, C343.2, C344.2, JP430.9, SJ256.3, SJ257.1, SJ258.1, U86.18
GND86: C345.2, C346.2, C347.2, C348.2, JP435.9, SJ259.3, SJ260.1, SJ261.1, U87.18
GND87: C349.2, C350.2, C351.2, C352.2, JP440.9, SJ262.3, SJ263.1, SJ264.1, U88.18
GND88: C353.2, C354.2, C355.2, C356.2, JP445.9, SJ265.3, SJ266.1, SJ267.1, U89.18
GND89: C357.2, C358.2, C359.2, C360.2, JP450.9, SJ268.3, SJ269.1, SJ270.1, U90.18
GND90: C361.2, C362.2, C363.2, C364.2, JP455.9, SJ271.3, SJ272.1, SJ273.1, U91.18
GND91: C365.2, C366.2, C367.2, C368.2, JP460.9, SJ274.3, SJ275.1, SJ276.1, U92.18
GND92: C369.2, C370.2, C371.2, C372.2, JP465.9, SJ277.3, SJ278.1, SJ279.1, U93.18
GND93: C373.2, C374.2, C375.2, C376.2, JP470.9, SJ280.3, SJ281.1, SJ282.1, U94.18
GND94: C377.2, C378.2, C379.2, C380.2, JP475.9, SJ283.3, SJ284.1, SJ285.1, U95.18
GND95: C381.2, C382.2, C383.2, C384.2, JP480.9, SJ286.3, SJ287.1, SJ288.1, U96.18
INT: JP6.8, U1.12
INT1: JP10.8, U2.12
INT2: JP15.8, U3.12
INT3: JP20.8, U4.12
INT4: JP25.8, U5.12
INT5: JP30.8, U6.12
INT6: JP35.8, U7.12
INT7: JP40.8, U8.12
INT8: JP45.8, U9.12
INT9: JP50.8, U10.12
INT10: JP55.8, U11.12
INT11: JP60.8, U12.12
INT12: JP65.8, U13.12
INT13: JP70.8, U14.12
INT14: JP75.8, U15.12
INT15: JP80.8, U16.12
INT16: JP85.8, U17.12
INT17: JP90.8, U18.12
INT18: JP95.8, U19.12
INT19: JP100.8, U20.12
INT20: JP105.8, U21.12
INT21: JP110.8, U22.12
INT22: JP115.8, U23.12
INT23: JP120.8, U24.12
INT24: JP125.8, U25.12
INT25: JP130.8, U26.12
INT26: JP135.8, U27.12
INT27: JP140.8, U28.12
INT28: JP145.8, U29.12
INT29: JP150.8, U30.12
INT30: JP155.8, U31.12
INT31: JP160.8, U32.12
INT32: JP165.8, U33.12
INT33: JP170.8, U34.12
INT34: JP175.8, U35.12
INT35: JP180.8, U36.12
INT36: JP185.8, U37.12
INT37: JP190.8, U38.12
INT38: JP195.8, U39.12
INT39: JP200.8, U40.12
INT40: JP205.8, U41.12
INT41: JP210.8, U42.12
INT42: JP215.8, U43.12
INT43: JP220.8, U44.12
INT44: JP225.8, U45.12
INT45: JP230.8, U46.12
INT46: JP235.8, U47.12
INT47: JP240.8, U48.12
INT48: JP245.8, U49.12
INT49: JP250.8, U50.12
INT50: JP255.8, U51.12
INT51: JP260.8, U52.12
INT52: JP265.8, U53.12
INT53: JP270.8, U54.12
INT54: JP275.8, U55.12
INT55: JP280.8, U56.12
INT56: JP285.8, U57.12
INT57: JP290.8, U58.12
INT58: JP295.8, U59.12
INT59: JP300.8, U60.12
INT60: JP305.8, U61.12
INT61: JP310.8, U62.12
INT62: JP315.8, U63.12
INT63: JP320.8, U64.12
INT64: JP325.8, U65.12
INT65: JP330.8, U66.12
INT66: JP335.8, U67.12
INT67: JP340.8, U68.12
INT68: JP345.8, U69.12
INT69: JP350.8, U70.12
INT70: JP355.8, U71.12
INT71: JP360.8, U72.12
INT72: JP365.8, U73.12
INT73: JP370.8, U74.12
INT74: JP375.8, U75.12
INT75: JP380.8, U76.12
INT76: JP385.8, U77.12
INT77: JP390.8, U78.12
INT78: JP395.8, U79.12
INT79: JP400.8, U80.12
INT80: JP405.8, U81.12
INT81: JP410.8, U82.12
INT82: JP415.8, U83.12
INT83: JP420.8, U84.12
INT84: JP425.8, U85.12
INT85: JP430.8, U86.12
INT86: JP435.8, U87.12
INT87: JP440.8, U88.12
INT88: JP445.8, U89.12
INT89: JP450.8, U90.12
INT90: JP455.8, U91.12
INT91: JP460.8, U92.12
INT92: JP465.8, U93.12
INT93: JP470.8, U94.12
INT94: JP475.8, U95.12
INT95: JP480.8, U96.12
unnamed: C6.1, U2.20
unnamed: C5.1, U2.10
unnamed: C2.1, U1.20
unnamed: C10.1, U3.20
unnamed: C1.1, U1.10
unnamed: C9.1, U3.10
unnamed: C14.1, U4.20
unnamed: C13.1, U4.10
unnamed: C18.1, U5.20
unnamed: C17.1, U5.10
unnamed: C22.1, U6.20
unnamed: C21.1, U6.10
unnamed: C26.1, U7.20
unnamed: C25.1, U7.10
unnamed: C30.1, U8.20
unnamed: C29.1, U8.10
unnamed: C34.1, U9.20
unnamed: C33.1, U9.10
unnamed: C38.1, U10.20
unnamed: C37.1, U10.10
unnamed: C42.1, U11.20
unnamed: C41.1, U11.10
unnamed: C46.1, U12.20
unnamed: C45.1, U12.10
unnamed: C50.1, U13.20
unnamed: C49.1, U13.10
unnamed: C54.1, U14.20
unnamed: C53.1, U14.10
unnamed: C58.1, U15.20
unnamed: C57.1, U15.10
unnamed: C62.1, U16.20
unnamed: C61.1, U16.10
unnamed: C66.1, U17.20
unnamed: C65.1, U17.10
unnamed: C70.1, U18.20
unnamed: C69.1, U18.10
unnamed: C74.1, U19.20
unnamed: C73.1, U19.10
unnamed: C78.1, U20.20
unnamed: C77.1, U20.10
unnamed: C82.1, U21.20
unnamed: C81.1, U21.10
unnamed: C86.1, U22.20
unnamed: C85.1, U22.10
unnamed: C90.1, U23.20
unnamed: C89.1, U23.10
unnamed: C94.1, U24.20
unnamed: C93.1, U24.10
unnamed: C98.1, U25.20
unnamed: C97.1, U25.10
unnamed: C102.1, U26.20
unnamed: C101.1, U26.10
unnamed: C106.1, U27.20
unnamed: C105.1, U27.10
unnamed: C110.1, U28.20
unnamed: C109.1, U28.10
unnamed: C114.1, U29.20
unnamed: C113.1, U29.10
unnamed: C118.1, U30.20
unnamed: C117.1, U30.10
unnamed: C122.1, U31.20
unnamed: C121.1, U31.10
unnamed: C126.1, U32.20
unnamed: C125.1, U32.10
unnamed: C130.1, U33.20
unnamed: C129.1, U33.10
unnamed: C134.1, U34.20
unnamed: C133.1, U34.10
unnamed: C138.1, U35.20
unnamed: C137.1, U35.10
unnamed: C142.1, U36.20
unnamed: C141.1, U36.10
unnamed: C146.1, U37.20
unnamed: C145.1, U37.10
unnamed: C150.1, U38.20
unnamed: C149.1, U38.10
unnamed: C154.1, U39.20
unnamed: C153.1, U39.10
unnamed: C158.1, U40.20
unnamed: C157.1, U40.10
unnamed: C162.1, U41.20
unnamed: C161.1, U41.10
unnamed: C166.1, U42.20
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
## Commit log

2013-06-12 BRD+SCH files from KENTRO v.11
2013-06-13 Package 0402 >>0603, cleaned up schematic, gitignore
2013-06-18 Same except moved "AD0" silk off jumper pads
2013-06-24 Cleaned up silk and schematic
    -Moved via so that it is not under the "sync" or the "AD0" silk
    -Changed Z-axis silk to circle w/ dot (from circle with X)
    -added changes (code) on schematic
2013-06-24 changed bottom copper to V12 from V11
2013-07-11 Production ready for v12
    created panel
2013-07-15 Fixed Air-wire on ADO line
2013-07-15 Fixed VIA on ADO line
2013-07-15 Created Panels
    Created two separate panels. 1 giant for the MYDATA, 1 regular for the
    manncorp machines.
2013-07-23 Fixed formatting issues on schematic and board file
2013-07-23 Update README.md
    Adding in license info and general repo information.
2015-08-03 changed panel for better solder printing
2025-06-27 Update README.md
    Updating link
